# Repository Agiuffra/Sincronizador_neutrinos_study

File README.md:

# Sincronizador

**Implementación del sincronizador en VHDL**

En este proyecto de Vivado, se encuentran los bloques relacionados con la sincronización del proyecto. Estos se pueden ver en la siguiente imagen, marcados dentro de un cuadrante de color morado.

Los bloques a implementar son: *reset detector*, *fine time counter*, *RTC driver* y *time stamp control*.

## Bloques

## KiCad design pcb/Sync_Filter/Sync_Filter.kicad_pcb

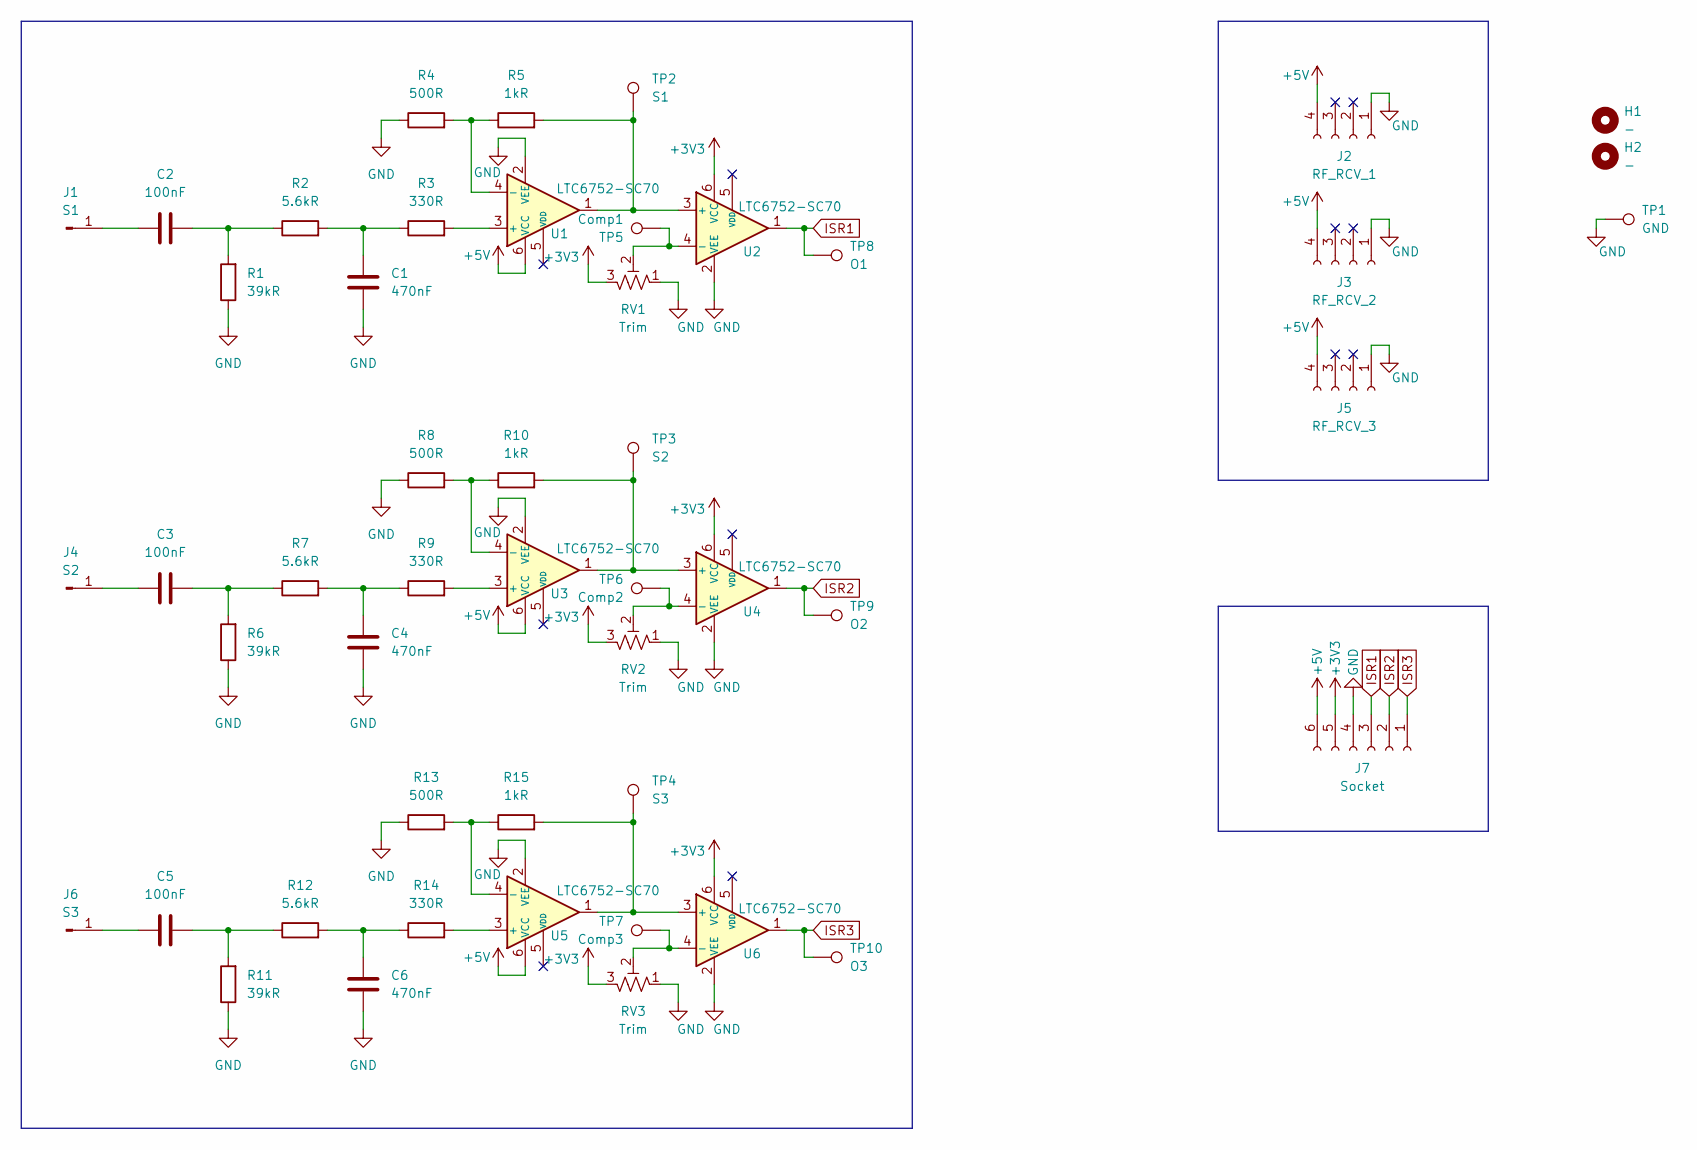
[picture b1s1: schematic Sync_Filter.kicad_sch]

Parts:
C1, C4, C6: 470nF; C_Disc_D4.7mm_W2.5mm_P5.00mm
C2, C3, C5: 100nF; C_Disc_D5.0mm_W2.5mm_P2.50mm
H1, H2: -; MountingHole_3.2mm_M3_ISO14580
J1: S1; PinHeader_1x01_P2.54mm_Vertical
J2: RF_RCV_1; PinSocket_1x04_P2.54mm_Vertical
J3: RF_RCV_2; PinSocket_1x04_P2.54mm_Vertical
J4: S2; PinHeader_1x01_P2.54mm_Vertical
J5: RF_RCV_3; PinSocket_1x04_P2.54mm_Vertical
J6: S3; PinHeader_1x01_P2.54mm_Vertical
J7: Socket; PinSocket_1x06_P2.54mm_Vertical
R1, R6, R11: 39kR; R_Axial_DIN0204_L3.6mm_D1.6mm_P2.54mm_Vertical
R2, R7, R12: 5.6kR; R_Axial_DIN0204_L3.6mm_D1.6mm_P2.54mm_Vertical
R3, R9, R14: 330R; R_Axial_DIN0204_L3.6mm_D1.6mm_P2.54mm_Vertical
R4, R8, R13: 500R; R_Axial_DIN0204_L3.6mm_D1.6mm_P2.54mm_Vertical
R5, R10, R15: 1kR; R_Axial_DIN0204_L3.6mm_D1.6mm_P2.54mm_Vertical
RV1, RV2, RV3: Trim; 282S
TP1: GND; PinHeader_1x01_P2.54mm_Vertical
TP2: S1; PinHeader_1x01_P2.54mm_Vertical
TP3: S2; PinHeader_1x01_P2.54mm_Vertical
TP4: S3; PinHeader_1x01_P2.54mm_Vertical
TP5: Comp1; PinHeader_1x01_P2.54mm_Vertical
TP6: Comp2; PinHeader_1x01_P2.54mm_Vertical
TP7: Comp3; PinHeader_1x01_P2.54mm_Vertical
TP8: O1; PinHeader_1x01_P2.54mm_Vertical
TP9: O2; PinHeader_1x01_P2.54mm_Vertical
TP10: O3; PinHeader_1x01_P2.54mm_Vertical
U1, U2, U3, U4, U5, U6: LTC6752-SC70; SOT-363_SC-70-6

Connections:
+3V3: J7.5, RV1.3, RV2.3, RV3.3, U2.6 (VCC), U4.6 (VCC), U6.6 (VCC)
+5V: J2.4, J3.4, J5.4, J7.6, U1.6 (VCC), U3.6 (VCC), U5.6 (VCC)
GND: C1.2, C4.2, C6.2, J2.1, J3.1, J5.1, J7.4, R1.1, R4.1, R6.1, R8.1, R11.1, R13.1, RV1.1, RV2.1, RV3.1, TP1.1, U1.2 (VEE), U2.2 (VEE), U3.2 (VEE), U4.2 (VEE), U5.2 (VEE), U6.2 (VEE)
ISR1: J7.3, TP8.1, U2.1
ISR2: J7.2, TP9.1, U4.1
ISR3: J7.1, TP10.1, U6.1
unnamed: C1.1, R2.2, R3.1
unnamed: C2.2, R1.2, R2.1
unnamed: C3.2, R6.2, R7.1
unnamed: C4.1, R7.2, R9.1
unnamed: C5.2, R11.2, R12.1
unnamed: C6.1, R12.2, R14.1
unnamed: C2.1, J1.1
unnamed: C3.1, J4.1
unnamed: C5.1, J6.1
unnamed: R3.2, U1.3 (+)
unnamed: R4.2, R5.1, U1.4 (-)
unnamed: R5.2, TP2.1, U1.1, U2.3 (+)
unnamed: RV1.2, TP5.1, U2.4 (-)
unnamed: R9.2, U3.3 (+)
unnamed: R8.2, R10.1, U3.4 (-)
unnamed: R10.2, TP3.1, U3.1, U4.3 (+)
unnamed: RV2.2, TP6.1, U4.4 (-)
unnamed: R14.2, U5.3 (+)
unnamed: R13.2, R15.1, U5.4 (-)
unnamed: R15.2, TP4.1, U5.1, U6.3 (+)
unnamed: RV3.2, TP7.1, U6.4 (-)

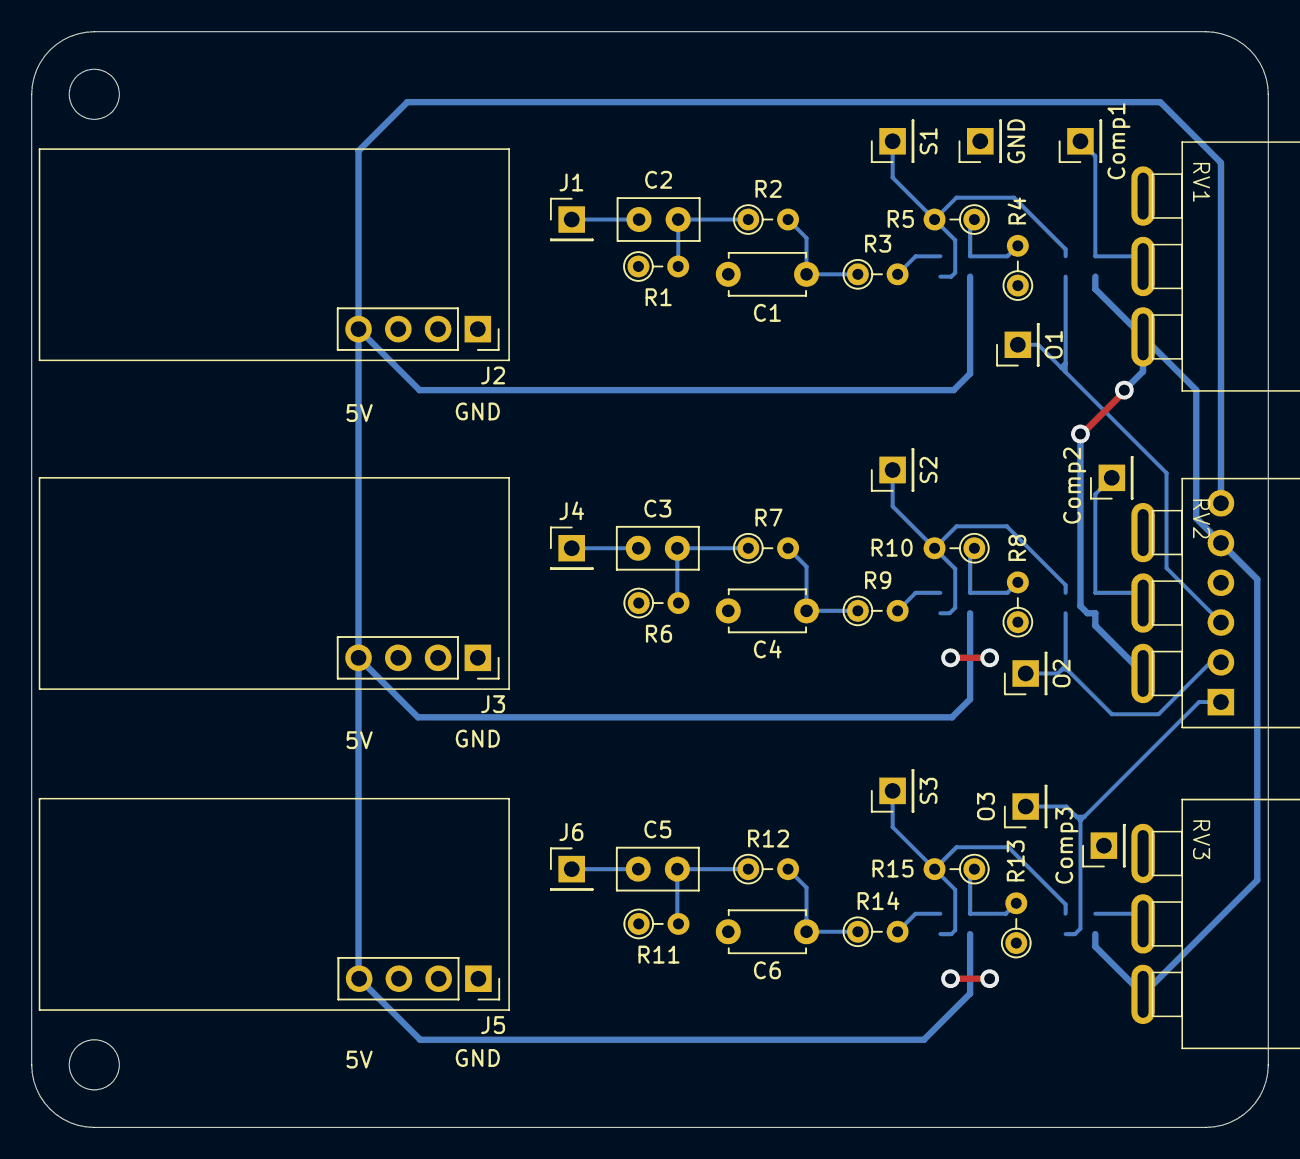
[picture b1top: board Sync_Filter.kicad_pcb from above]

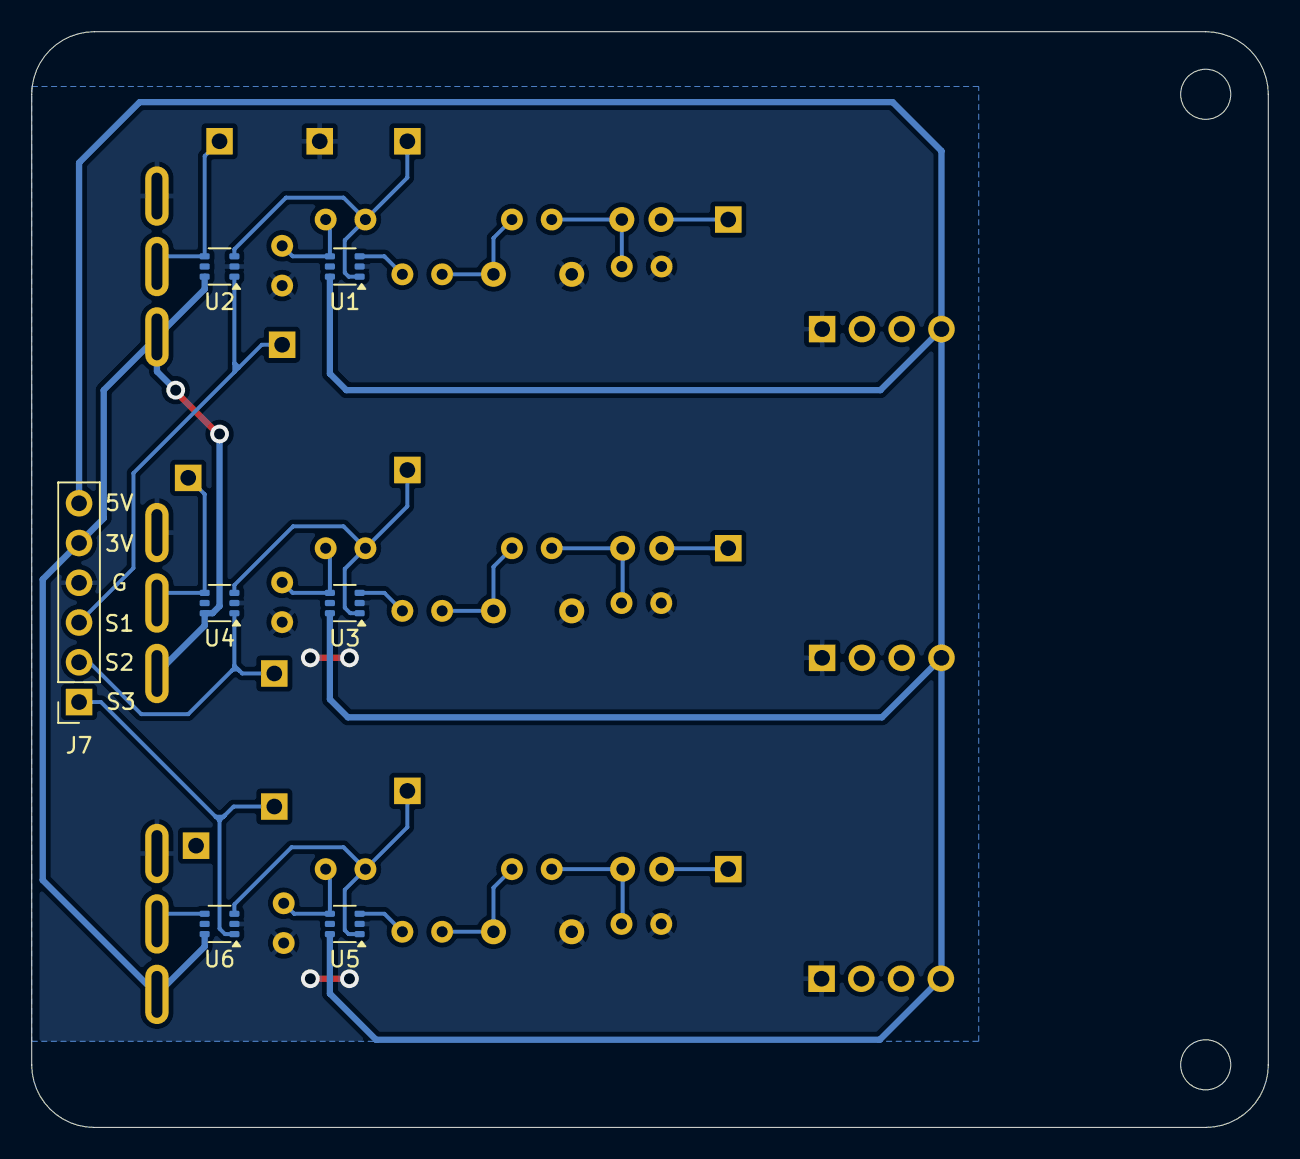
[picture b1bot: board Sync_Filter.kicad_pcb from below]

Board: 2 copper layers, 79.0 x 70.0 mm, 49 parts (7 on the bottom side), 27 nets.

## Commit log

2025-01-08 Actualizacion README
2025-01-08 Reset detector funcionando
2025-01-10 Sim Integrador
2025-01-10 UART ordenable
2025-01-13 TSC completo - VALIDAR
2025-01-13 Sim por terminar
2025-01-13 VHDL funciona SIM
2025-01-13 Actualiza gitignore
2025-01-13 VHDL imp func
2025-01-16 Sim Circuito 2
2025-01-16 Filter Sim go
2025-01-17 sim updt
2025-02-05 PCB y SIM updt
